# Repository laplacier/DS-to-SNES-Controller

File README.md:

# DS-to-SNES-Controller
 PCB for converting a DS shell into a SNES controller.

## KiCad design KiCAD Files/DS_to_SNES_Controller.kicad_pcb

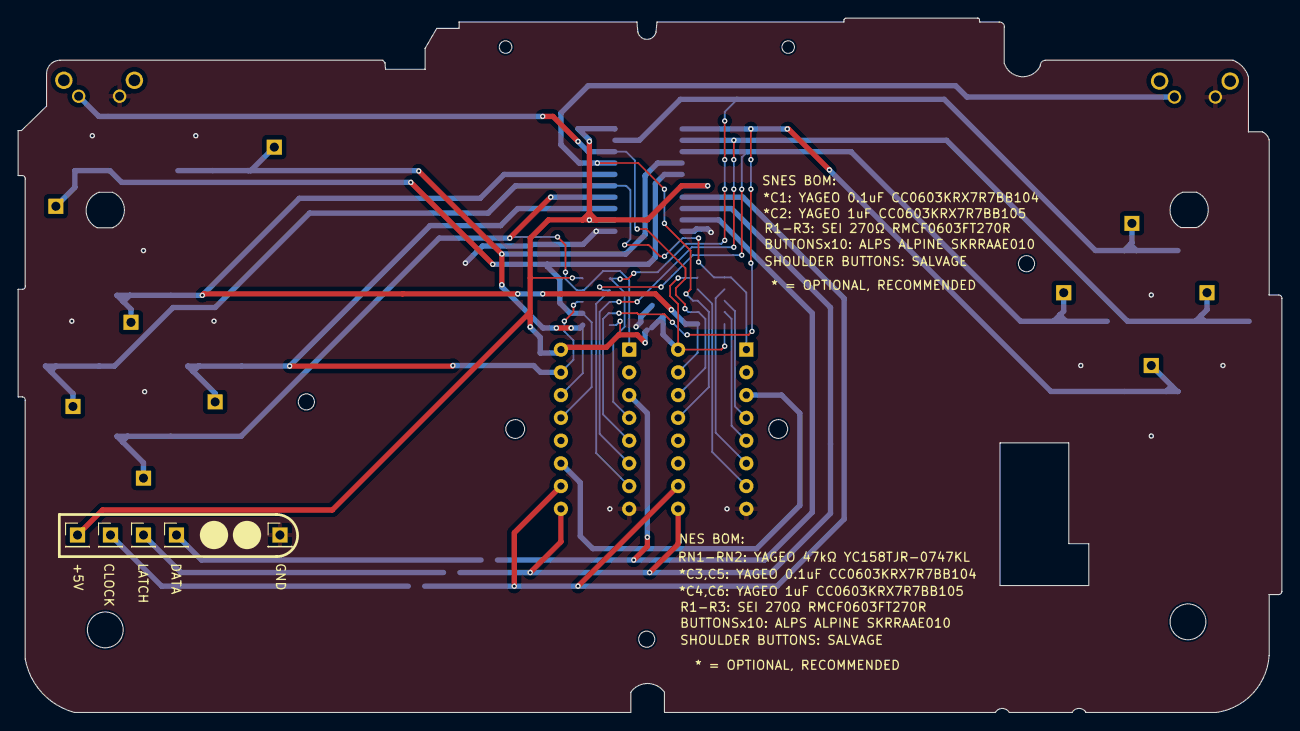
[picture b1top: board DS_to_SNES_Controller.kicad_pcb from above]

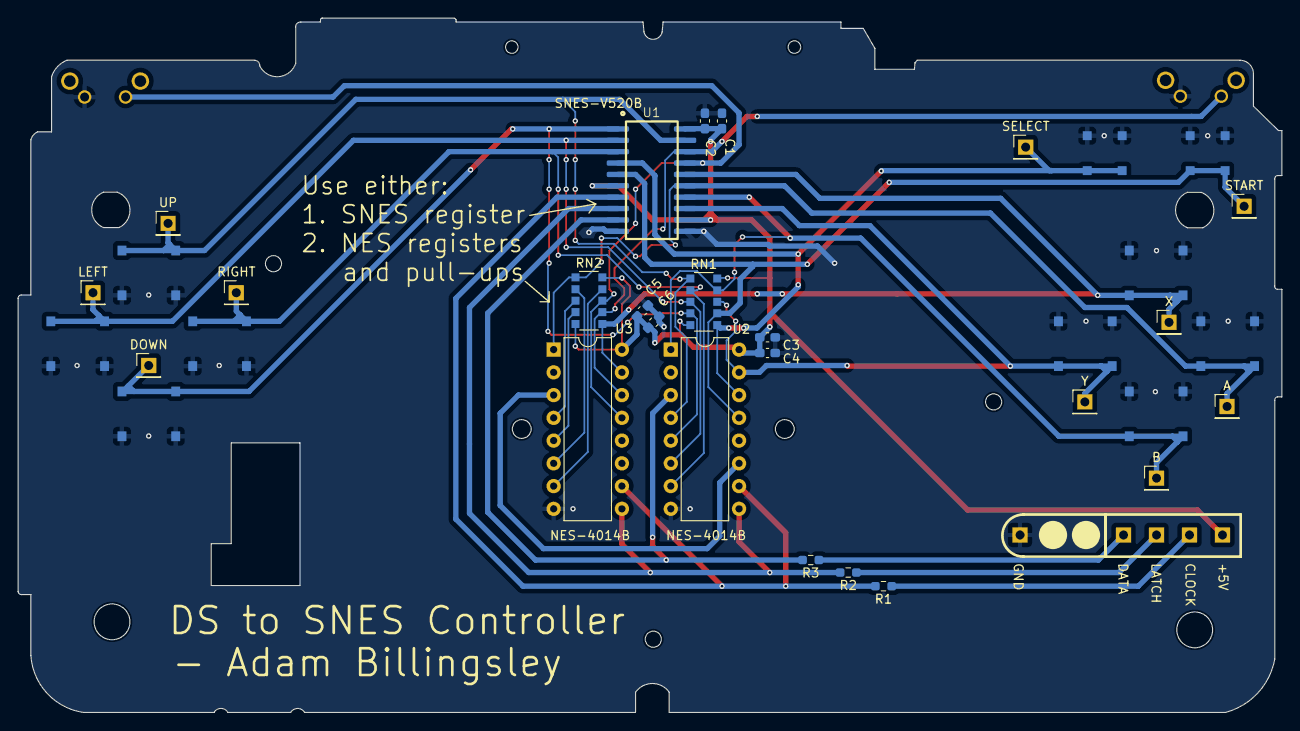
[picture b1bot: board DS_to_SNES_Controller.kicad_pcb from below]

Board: 2 copper layers, 141.1 x 77.5 mm, 50 parts (34 on the bottom side), 25 nets.

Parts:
@HOLE0, @HOLE1, @HOLE2, @HOLE3, @HOLE4, @HOLE5, @HOLE6, @HOLE7, @HOLE8: (no value)
A: Conn_01x01_Pin; PinHeader_1x01_P2.54mm_Vertical
B: Conn_01x01_Pin; PinHeader_1x01_P2.54mm_Vertical
BUT_A0: BUTTON
BUT_B0: BUTTON
BUT_DN0: BUTTON
BUT_L0: BUTTON_LR
BUT_LF0: BUTTON
BUT_R0: BUTTON_LR
BUT_RG0: BUTTON
BUT_SEL0: BUTTON_SMALL
BUT_ST0: BUTTON_SMALL
BUT_UP0: BUTTON
BUT_X0: BUTTON
BUT_Y0: BUTTON
C1, C3, C5: 0.1uF; C_0603_1608Metric_Pad1.08x0.95mm_HandSolder
C2, C4, C6: 1uF; C_0603_1608Metric_Pad1.08x0.95mm_HandSolder
DOWN: Conn_01x01_Pin; PinHeader_1x01_P2.54mm_Vertical
J1, J2, J3, J4, J5: Conn_01x01_Pin; PinHeader_1x01_P2.54mm_Vertical
LEFT: Conn_01x01_Pin; PinHeader_1x01_P2.54mm_Vertical
R1, R2, R3: 270Ω; R_0603_1608Metric_Pad0.98x0.95mm_HandSolder
RIGHT: Conn_01x01_Pin; PinHeader_1x01_P2.54mm_Vertical
RN1, RN2: 47kΩ; R_Array_Convex_5x1206
SELECT: Conn_01x01_Pin; PinHeader_1x01_P2.54mm_Vertical
START: Conn_01x01_Pin; PinHeader_1x01_P2.54mm_Vertical
U1: V520B-SNES
U2, U3: 4021; DIP-16_W7.62mm
UP: Conn_01x01_Pin; PinHeader_1x01_P2.54mm_Vertical
X: Conn_01x01_Pin; PinHeader_1x01_P2.54mm_Vertical
Y: Conn_01x01_Pin; PinHeader_1x01_P2.54mm_Vertical

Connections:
+5V: C1.1, C2.1, C3.1, C4.1, C5.1, C6.1, J1.1, RN1.5 (common), RN1.10 (common), RN2.5 (common), RN2.10 (common), U1.6 (VCC), U1.12 (VCC), U1.20 (VCC), U2.16 (VDD), U3.16 (VDD)
/A: A.1, BUT_A0.2, BUT_A0.3, RN2.1 (R1), U1.15 (A), U3.1 (D7)
/B: B.1, BUT_B0.2, BUT_B0.3, RN1.9 (R8), U1.14 (B), U2.1 (D7)
/CLK: R1.2, U1.7 (CLK), U2.10 (CP), U3.10 (CP)
/DAT: R3.2, U1.9 (DATA), U2.3 (Q7)
/DOWN: BUT_DN0.2, BUT_DN0.3, DOWN.1, RN1.4 (R4), U1.1 (DOWN), U2.5 (D2)
/LAT: R2.2, U1.8 (LATCH), U2.9 (PL), U3.9 (PL)
/LEFT: BUT_LF0.2, BUT_LF0.3, LEFT.1, RN1.3 (R3), U1.2 (LEFT), U2.6 (D1)
/RIGHT: BUT_RG0.2, BUT_RG0.3, RIGHT.1, RN1.2 (R2), U1.3 (RIGHT), U2.7 (D0)
/SELECT: BUT_SEL0.2, BUT_SEL0.3, RN1.6 (R5), SELECT.1, U1.4 (SELECT), U2.14 (D5)
/START: BUT_ST0.2, BUT_ST0.3, RN1.7 (R6), START.1, U1.5 (START), U2.13 (D4)
/UP: BUT_UP0.2, BUT_UP0.3, RN1.1 (R1), U1.19 (UP), U2.4 (D3), UP.1
/X: BUT_X0.2, BUT_X0.3, RN2.6 (R5), U1.16 (X), U3.15 (D6), X.1
/Y: BUT_Y0.2, BUT_Y0.3, RN1.8 (R7), U1.13 (Y), U2.15 (D6), Y.1
/ZL: BUT_R0.1, RN2.7 (R6), U1.18 (ZL), U3.14 (D5)
/ZR: BUT_L0.1, RN2.8 (R7), U1.17 (ZR), U3.13 (D4)
GND: BUT_A0.1, BUT_A0.4, BUT_B0.1, BUT_B0.4, BUT_DN0.1, BUT_DN0.4, BUT_L0.2, BUT_LF0.1, BUT_LF0.4, BUT_R0.2, BUT_RG0.1, BUT_RG0.4, BUT_SEL0.1, BUT_SEL0.4, BUT_ST0.1, BUT_ST0.4, BUT_UP0.1, BUT_UP0.4, BUT_X0.1, BUT_X0.4, BUT_Y0.1, BUT_Y0.4, C1.2, C2.2, C3.2, C4.2, C5.2, C6.2, J5.1, U1.10 (GND), U1.11 (GND), U2.8 (VSS), U3.8 (VSS)
unnamed: J2.1, R1.1
unnamed: J3.1, R2.1
unnamed: J4.1, R3.1
unnamed: RN2.2 (R2), U3.6 (D1)
unnamed: RN2.3 (R3), U3.4 (D3)
unnamed: RN2.4 (R4), U3.5 (D2)
unnamed: RN2.9 (R8), U3.7 (D0)
unnamed: U2.11 (DS), U3.3 (Q7)

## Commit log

2024-08-15 Upload files
2024-09-13 Changed total layers to 2
2024-12-07 Updated PCBWay Gerber
